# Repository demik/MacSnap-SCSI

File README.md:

# MacSnap SCSI

The MacSnap SCSI is an upgrade for the Macintosh 512K(e) It includes a SCSI controller and is designed to plug into the ROM slots
It was developed by Dove Computer Corporation. This is a REcreation with a few improvements.

<br />
<br />
<div align = center>
	
</div>

<br />
<br />
<br />
<br />

## [![Button Documentation]][Documentation]
- Kikad Files are located [here](EDA/REloaded), as well with building instructions for the REloaded board
- PLD files are located [here](PLD)
- Gerbers files are in the [release section](https://github.com/demik/MacSnap-SCSI/releases/download/v2.1/MacSnap_SCSI_Reloaded_2.1.zip)
- Schematic in PDF form is [here](https://github.com/demik/MacSnap-SCSI/blob/main/EDA/REloaded/MacSnap%20SCSI.pdf)

<!----------------------------------------------------------------------------->

[Documentation]: https://github.com/demik/MacSnap-SCSI/tree/main/EDA/REloaded/README.md

<!-------------------------------[ Buttons ]----------------------------------->

[Button Documentation]: https://img.shields.io/badge/Documentation-FFDD21?style=for-the-badge&logoColor=white&logo=opensourcehardware

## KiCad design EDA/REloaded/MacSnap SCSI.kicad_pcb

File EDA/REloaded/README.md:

# MacSnap SCSI Reloaded

This is a simple design clone to the original, using mostly all through hole components. It's designed this way to be period correct and easy to build for people who don't like soldering SMD components. The only SMD component is the 2.85V voltage regulator for SCSI termination.
Footprint is very similar. Like the original, the SCSI is provided through a LPT header.

The board has a few improvements:
- provides power to SCSI devices
- active SCSI termination
- voltage supervisor / reset ciruit

This folder contains the source KiKad files for this board.

## ![Button BOM]
### Mandatory

Here is the BOM for the board. Part number are what was tested on prototypes board but you may find alternatives easily, especially resistors and sockets

| Reference(s)          | Value      | Quantity | Notes                                  | Part number              |
|-----------------------|------------|----------|----------------------------------------|--------------------------|
| C1-2, C6, C7, C13-14  | 100nF      | 6        | Axial ceramic capacitor X7R            | Kemet C412C104K5R5TA7200 |
| C4                    | 1500pF     | 1        | Axial ceramic capacitor X7R 10%        | Kemet C410C152K1R5TA     |
| C8-11                 | 10uF       | 4        | Tantalum radial capacitor 2.5mm pitch  | Thomsen 481726           |
| D2                    | 1N5817     | 1        | Schottky Diode DO-15 20V               | Diotec 1N5817            |
| J1                    | 26 pins    | 1        | low profile shrouded IDC header        | TE Conn 5103309-6        |
| R1, R3                | 10kΩ       | 2        | standard 0.25W carbon film resistor    | TRU CFR0W4J0103          |
| R4                    | 470Ω       | 1        | standard 0.25W carbon film resistor    | TRU CFR0W4J0471          |
| R5, R6                | 47Ω        | 2        | standard 0.25W carbon film resistor    | TRU CFR0W4J0470          |
| RN1, RN2              | 110Ω       | 2        | 10 pins bussed resistor array          | Bourns 4610X-101-111LF   |
| U5, U6                | 16V8       | 2        | Programmable Logic Devices 15ns        | Microchip ATF16V8B-15PU  |
| U7                    | 53C80      | 1        | SCSI Interface IC 3MB/SEC CMOS SCSI I  | Zilog Z53C8003VSG        |
| U8                    | LDO        | 1        | 800mA SCSI-5 Active Terminator         | onsemi MC34268DR2G       |
| U10                   | RESET      | 1        | Supervisory Circuits 5V EconoReset     | DS1233D-15+              |
| -                     | LPT        | 1        | Parallel DB25 Female LPT to IDC 26-pin | ?? eBay / Amazon         |
| -                     | 14 pins    | 4        | Machine Pin break away header          | ?? eBay / Amazon         |
| Socket                | DIP-20     | 2        | THT DIP-20 socket                      | TRU TC-A 20-LC-TT-203    |
| Socket                | DIP-28     | 2        | THT DIP-28 socket                      | TRU TC-A 28-LC-TT-203    |
| Socket                | PLCC-44    | 1        | THT PLCC-44 socket                     | TRU TC-A-CCS 044-Z-T-203 |

Using sockets is recommended because it will allow you to reclaim both ROMs (to put back into factory) and PLDs

### Alternate

Both the 53C80 SCSI chip and MC34268 are obsolete components. NCR5380 in PLCC package is a working substitute. As for the active terminator LDO, there is an alternate build which consist of the following components:

| Reference(s)          | Value      | Quantity | Notes                                  | Part number              |
|-----------------------|------------|----------|----------------------------------------|--------------------------|
| U9                    | LDO        | 1        | LDO Voltage Regulators 800mA 2.85V     | A.D. LT1117CST-2.85      |
| C12                   | 10uF       | 1        | Tantalum radial capacitor 2.5mm pitch  | Thomsen 481726           |

When the LT1117CST build variant is used, do not populate U8

## ![Button Building]

PCB is 2 layers, the gerbers are avaible in the [release section](https://github.com/demik/MacSnap-SCSI/releases/download/v2.1/MacSnap_SCSI_Reloaded_2.1.zip)
You should be able to use any mainstream PCB manufacturer. Nothing special about this PCB, thickness should be 1.6mm

On JLCPCB, select _Create 2D barcode (Serial Number)_ to the option _Remove Order Number_. Others options to set:
- Printing: 2D barcode Only
- Code Type: QR Code
- Serial Number: MACSNAPSCSI
- QR Code Size: 10mm * 10mm
- QR Code Position: Specify Position

### Assembling

Building is straightworfard. You will need to start with the machine pin headers, then the following order is recommended:
- PDIP sockets
- axial resistors, axial capacitors
- resistors networks
- PLCC socket
- IDC header
- anything else left

### PLDs

You will need the following .jed files to program both ATF with this board:
- [DOV1b](../../PLD/DOV1B.jed) as DOV1b
- [DOV2_low](../../PLD/DOV2_low.jed) as DOV2

A TL866 II or T48 can program ATF16V8Bs just fine. Avoid ATF16V8BQL or ATF16V8C as this has not been tested and might lead into issues

### ROMs

Using real OEM ROMs is recommended. Replica ROMs do have different access timings, source and sink power capabilities, and thus may not work well with the MacSnap SCSI.
The following OEM sets have been tested without issues: 
- 342-0341-B & 342-0342-A
- 342-0341-C + 342-0342-B

<!-------------------------------[ Buttons ]----------------------------------->

[Button BOM]: https://img.shields.io/badge/BOM-FFDD21?style=for-the-badge&logoColor=white&logo=BookStack
[Button Building]: https://img.shields.io/badge/Building-FFDD21?style=for-the-badge&logoColor=white&logo=opensourcehardware

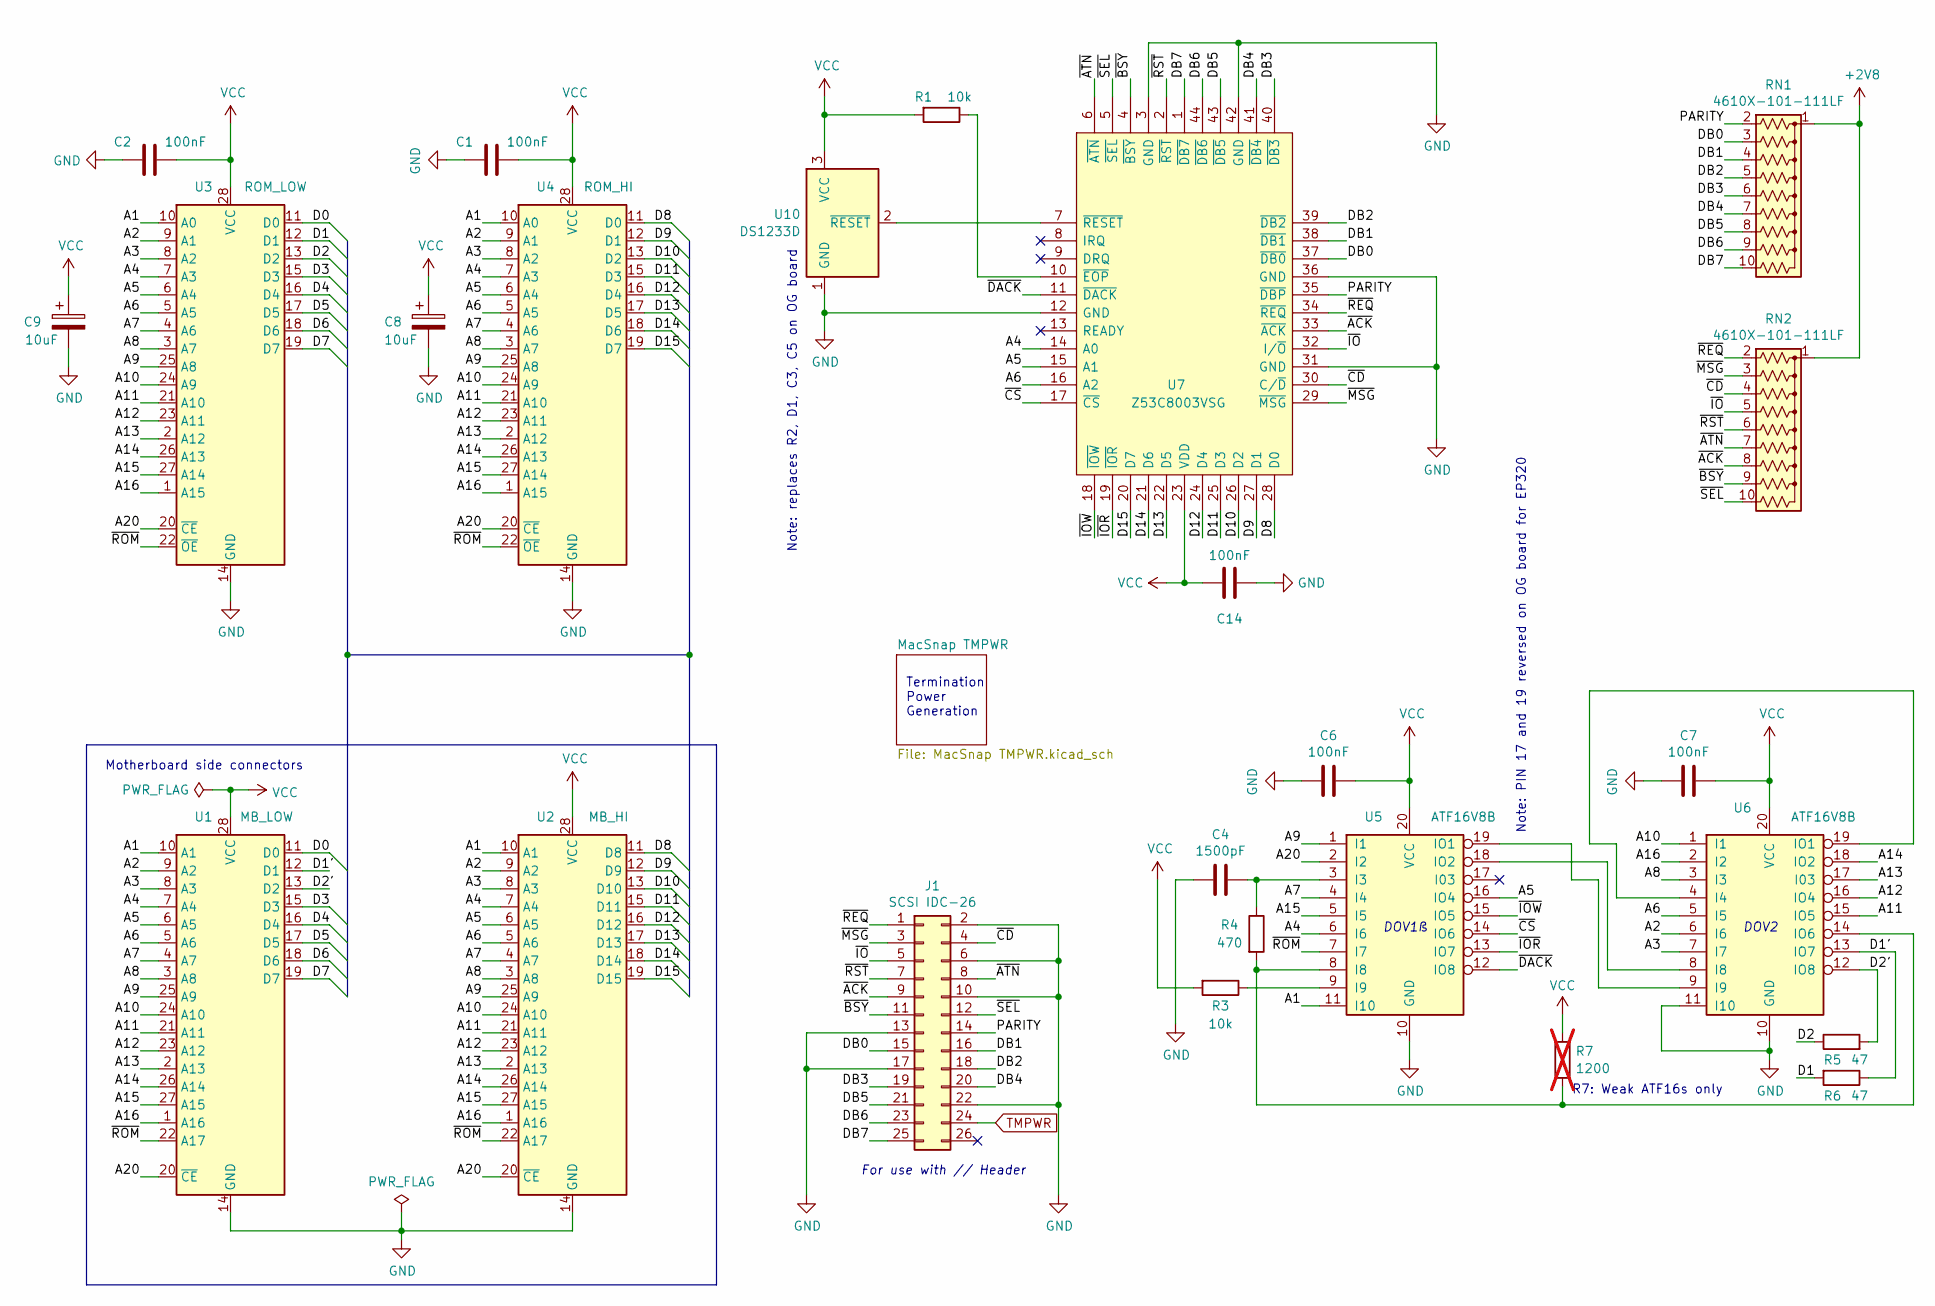
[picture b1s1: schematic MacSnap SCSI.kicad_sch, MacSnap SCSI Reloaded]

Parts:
C1, C2, C6, C7: 100nF; C_Axial_L3.8mm_D2.6mm_P7.50mm_Horizontal
C4: 1500pF; C_Axial_L3.8mm_D2.6mm_P7.50mm_Horizontal
C8, C9: 10uF; CP_Radial_Tantal_D4.5mm_P2.50mm
C14: 100nF; C_Axial_L3.8mm_D2.6mm_P10.00mm_Horizontal
J1: SCSI IDC-26; IDC-Header_2x13_P2.54mm_Vertical
R1, R3: 10k; R_Axial_DIN0207_L6.3mm_D2.5mm_P10.16mm_Horizontal
R4: 470; R_Axial_DIN0207_L6.3mm_D2.5mm_P10.16mm_Horizontal
R5, R6: 47; R_Axial_DIN0207_L6.3mm_D2.5mm_P10.16mm_Horizontal
R7: 1200; R_Axial_DIN0207_L6.3mm_D2.5mm_P10.16mm_Horizontal; not fitted
RN1, RN2: 4610X-101-111LF; R_Array_SIP10
U1: MB_LOW; DIP-28_W15.24mm_Piggy
U2: MB_HI; DIP-28_W15.24mm_Piggy
U3: ROM_LOW; DIP-28_W15.24mm_Socket
U4: ROM_HI; DIP-28_W15.24mm_Socket
U5, U6: ATF16V8B; DIP-20_W7.62mm
U7: Z53C8003VSG; PLCC-44_THT-Socket; Mouser Part Number 692-Z53C8003VSG
U10: DS1233D; TO-92_HandSolder

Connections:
+2V8: RN1.1 (common), RN2.1 (common); also elsewhere on the board
/A1: U1.10 (A1), U2.10 (A1), U3.10 (A0), U4.10 (A0), U5.11 (I10)
/A2: U1.9 (A2), U2.9 (A2), U3.9 (A1), U4.9 (A1), U6.6 (I6)
/A3: U1.8 (A3), U2.8 (A3), U3.8 (A2), U4.8 (A2), U6.7 (I7)
/A4: U1.7 (A4), U2.7 (A4), U3.7 (A3), U4.7 (A3), U5.6 (I6), U7.14 (A0)
/A5: U1.6 (A5), U2.6 (A5), U3.6 (A4), U4.6 (A4), U5.16 (IO4), U7.15 (A1)
/A6: U1.5 (A6), U2.5 (A6), U3.5 (A5), U4.5 (A5), U6.5 (I5), U7.16 (A2)
/A7: U1.4 (A7), U2.4 (A7), U3.4 (A6), U4.4 (A6), U5.4 (I4)
/A8: U1.3 (A8), U2.3 (A8), U3.3 (A7), U4.3 (A7), U6.3 (I3)
/A9: U1.25 (A9), U2.25 (A9), U3.25 (A8), U4.25 (A8), U5.1 (I1)
/A10: U1.24 (A10), U2.24 (A10), U3.24 (A9), U4.24 (A9), U6.1 (I1)
/A11: U1.21 (A11), U2.21 (A11), U3.21 (A10), U4.21 (A10), U6.15 (IO5)
/A12: U1.23 (A12), U2.23 (A12), U3.23 (A11), U4.23 (A11), U6.16 (IO4)
/A13: U1.2 (A13), U2.2 (A13), U3.2 (A12), U4.2 (A12), U6.17 (I03)
/A14: U1.26 (A14), U2.26 (A14), U3.26 (A13), U4.26 (A13), U6.18 (IO2)
/A15: U1.27 (A15), U2.27 (A15), U3.27 (A14), U4.27 (A14), U5.5 (I5)
/A16: U1.1 (A16), U2.1 (A16), U3.1 (A15), U4.1 (A15), U6.2 (I2)
/A20: U1.20 (~CE), U2.20 (~CE), U3.20 (~CE), U4.20 (~CE), U5.2 (I2)
/D0: U1.11 (D0), U3.11 (D0)
/D1: R6.2, U3.12 (D1)
/D1': R6.1, U1.12 (D1), U6.13 (IO7)
/D2: R5.1, U3.13 (D2)
/D2': R5.2, U1.13 (D2), U6.12 (IO8)
/D3: U1.15 (D3), U3.15 (D3)
/D4: U1.16 (D4), U3.16 (D4)
/D5: U1.17 (D5), U3.17 (D5)
/D6: U1.18 (D6), U3.18 (D6)
/D7: U1.19 (D7), U3.19 (D7)
/D8: U2.11 (D8), U4.11 (D0), U7.28 (D0)
/D9: U2.12 (D9), U4.12 (D1), U7.27 (D1)
/D10: U2.13 (D10), U4.13 (D2), U7.26 (D2)
/D11: U2.15 (D11), U4.15 (D3), U7.25 (D3)
/D12: U2.16 (D12), U4.16 (D4), U7.24 (D4)
/D13: U2.17 (D13), U4.17 (D5), U7.22 (D5)
/D14: U2.18 (D14), U4.18 (D6), U7.21 (D6)
/D15: U2.19 (D15), U4.19 (D7), U7.20 (D7)
/DB0: J1.15, RN1.3 (R2), U7.37 (~DB0)
/DB1: J1.16, RN1.4 (R3), U7.38 (~DB1)
/DB2: J1.18, RN1.5 (R4), U7.39 (~DB2)
/DB3: J1.19, RN1.6 (R5), U7.40 (~DB3)
/DB4: J1.20, RN1.7 (R6), U7.41 (~DB4)
/DB5: J1.21, RN1.8 (R7), U7.43 (~DB5)
/DB6: J1.23, RN1.9 (R8), U7.44 (~DB6)
/DB7: J1.25, RN1.10 (R9), U7.1 (~DB7)
/PARITY: J1.14, RN1.2 (R1), U7.35 (~DBP)
/~ACK: J1.9, RN2.8 (R7), U7.33 (~ACK)
/~ATN: J1.8, RN2.7 (R6), U7.6 (~ATN)
/~BSY: J1.11, RN2.9 (R8), U7.4 (~BSY)
/~CD: J1.4, RN2.4 (R3), U7.30 (C/~D)
/~CS: U5.14 (IO6), U7.17 (~CS)
/~DACK: U5.12 (IO8), U7.11 (~DACK)
/~IOR: U5.13 (IO7), U7.19 (~IOR)
/~IOW: U5.15 (IO5), U7.18 (~IOW)
/~IO: J1.5, RN2.5 (R4), U7.32 (I/~O)
/~MSG: J1.3, RN2.3 (R2), U7.29 (~MSG)
/~REQ: J1.1, RN2.2 (R1), U7.34 (~REQ)
/~ROM: U1.22 (A17), U2.22 (A17), U3.22 (~OE), U4.22 (~OE), U5.7 (I7)
/~RST: J1.7, RN2.6 (R5), U7.2 (~RST)
/~SEL: J1.12, RN2.10 (R9), U7.5 (~SEL)
GND: C1.2, C2.2, C4.2, C6.2, C7.2, C8.2, C9.2, C14.2, J1.2, J1.6, J1.10, J1.13, J1.17, J1.22, U1.14 (GND), U2.14 (GND), U3.14 (GND), U4.14 (GND), U5.10 (GND), U6.10 (GND), U6.11 (I10), U7.3 (GND), U7.12 (GND), U7.31 (GND), U7.36 (GND), U7.42 (GND), U10.1 (GND); also elsewhere on the board
unnamed: C4.1, R4.1, U5.3 (I3)
unnamed: R4.2, R7.2, U5.8 (I8), U6.14 (IO6)
unnamed: R3.1, U5.9 (I9)
unnamed: U5.19 (IO1), U6.9 (I9)
unnamed: U5.18 (IO2), U6.8 (I8)
unnamed: U6.4 (I4), U6.19 (IO1)
unnamed: R1.1, U7.10 (~EOP)
unnamed: U7.7 (~RESET), U10.2 (~RESET)
TMPWR: J1.24; also elsewhere on the board
VCC: C1.1, C2.1, C6.1, C7.1, C8.1, C9.1, C14.1, R1.2, R3.2, R7.1, U1.28 (VCC), U2.28 (VCC), U3.28 (VCC), U4.28 (VCC), U5.20 (VCC), U6.20 (VCC), U7.23 (VDD), U10.3 (VCC); also elsewhere on the board

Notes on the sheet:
R7: Weak ATF16s only
Termination Power Generation
DOV1ß
Note: replaces R2, D1, C3, C5 on OG board
Motherboard side connectors
For use with // Header
Note: PIN 17 and 19 reversed on OG board for EP320
DOV2

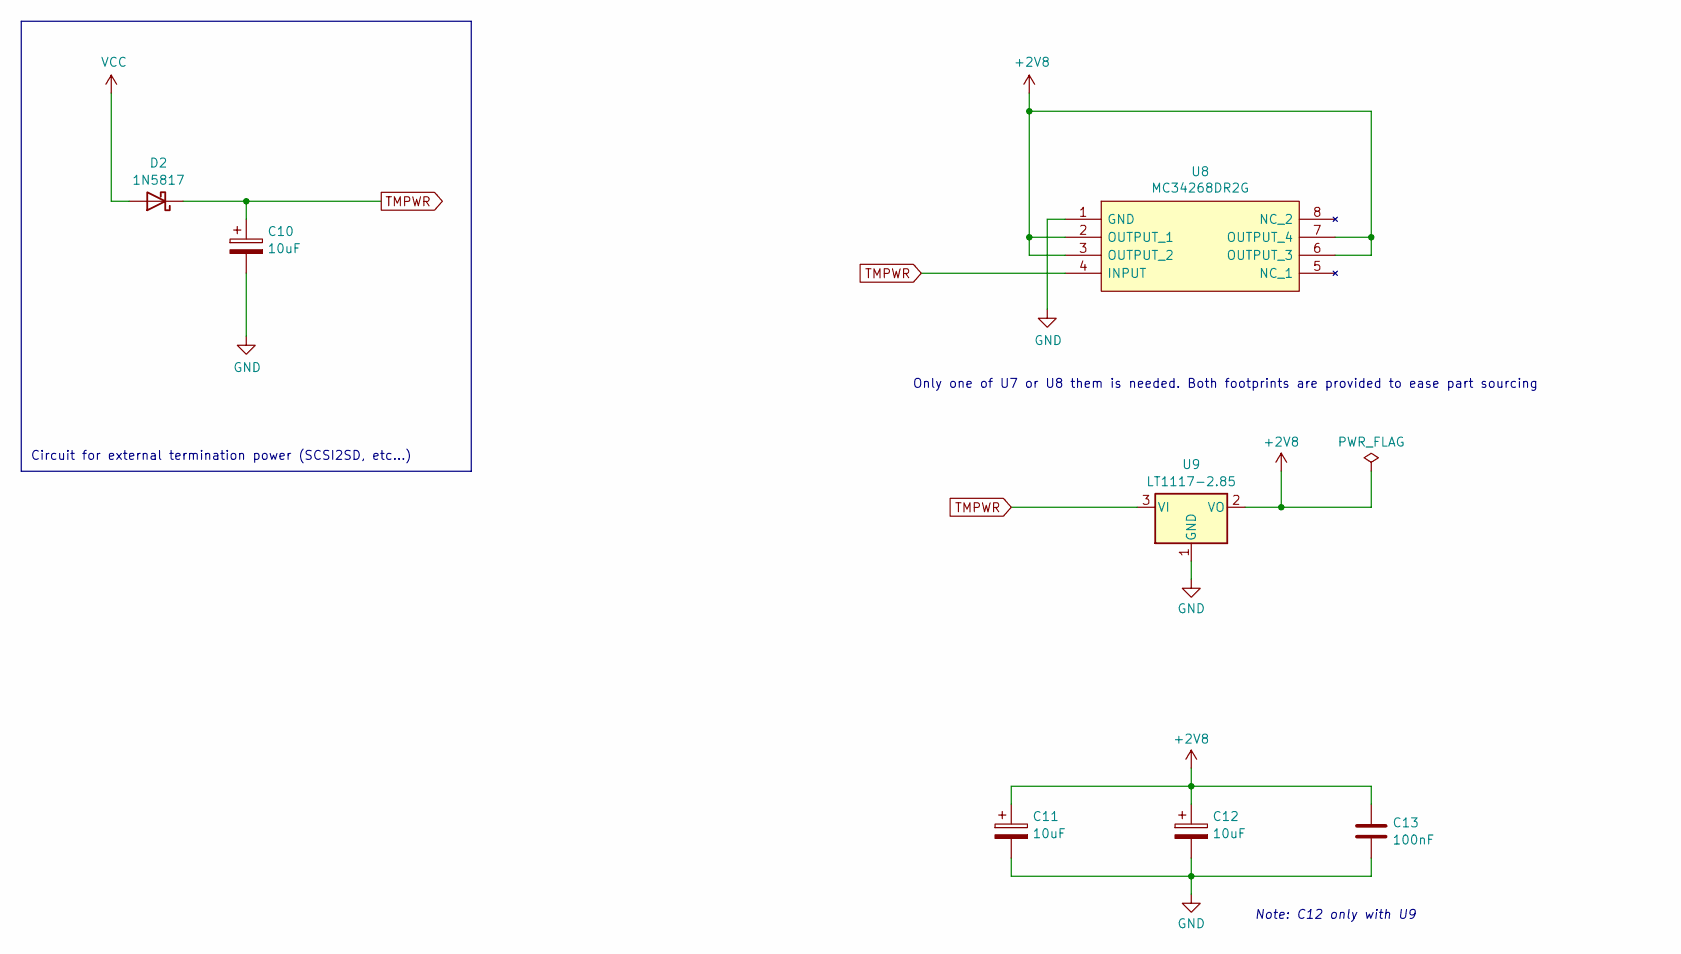
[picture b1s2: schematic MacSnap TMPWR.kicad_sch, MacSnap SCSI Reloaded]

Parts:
C10, C11, C12: 10uF; CP_Radial_Tantal_D4.5mm_P2.50mm
C13: 100nF; C_Axial_L3.8mm_D2.6mm_P10.00mm_Horizontal
D2: 1N5817; D_DO-41_SOD81_P10.16mm_Horizontal
U8: MC34268DR2G; SOIC-8_3.9x4.9mm_P1.27mm; Mouser Part Number 863-MC34268DR2G
U9: LT1117-2.85; SOT-223-3_TabPin2

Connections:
+2V8: C11.1, C12.1, C13.1, U8.2 (OUTPUT_1), U8.3 (OUTPUT_2), U8.6 (OUTPUT_3), U8.7 (OUTPUT_4), U9.2 (VO); also elsewhere on the board
GND: C10.2, C11.2, C12.2, C13.2, U8.1 (GND), U9.1 (GND); also elsewhere on the board
TMPWR: C10.1, D2.1 (K), U8.4 (INPUT), U9.3 (VI); also elsewhere on the board
VCC: D2.2 (A); also elsewhere on the board

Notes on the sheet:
Circuit for external termination power (SCSI2SD, etc…)
Only one of U7 or U8 them is needed. Both footprints are provided to ease part sourcing
Note: C12 only with U9

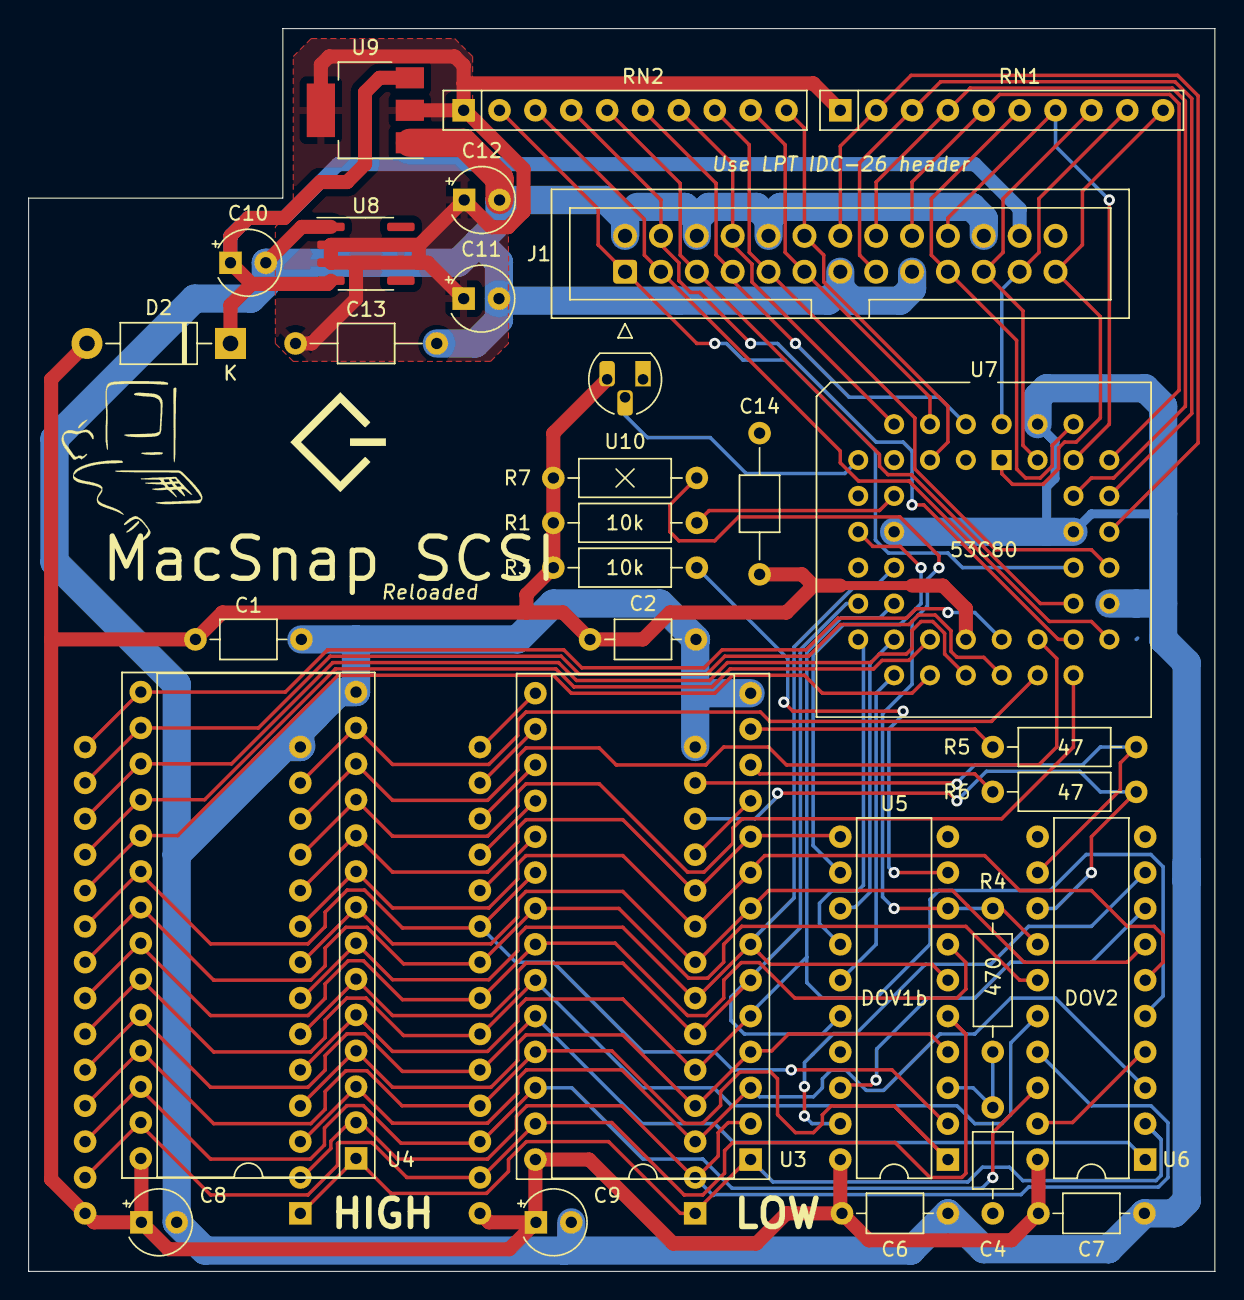
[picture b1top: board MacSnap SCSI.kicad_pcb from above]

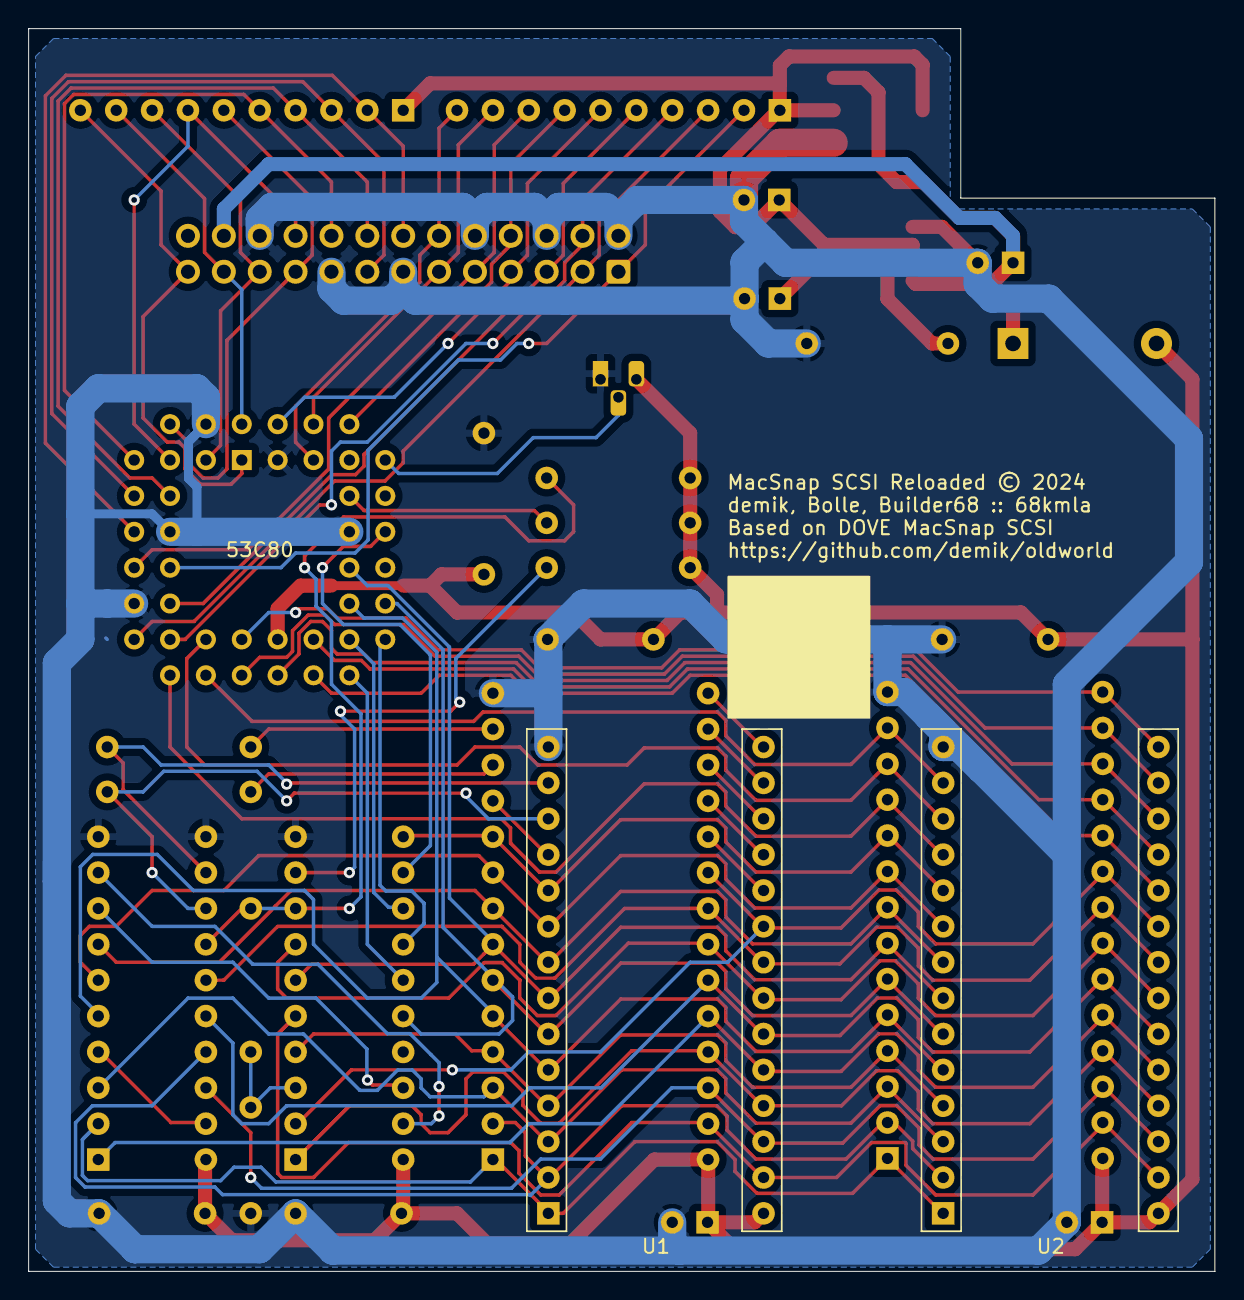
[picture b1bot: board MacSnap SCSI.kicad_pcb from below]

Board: 2 copper layers, 84.0 x 88.0 mm, 32 parts (2 on the bottom side), 70 nets.

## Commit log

2025-03-13 Update LICENSE
2025-03-13 added original schematics by Builder68
2025-03-14 added PLD stuff
2025-03-14 Initial REloaded public release
2025-03-15 removed backups files
2025-03-15 added main README.md
2025-03-15 formating
2025-03-16 added building instructions
2025-03-16 fixed image link
2025-03-16 fixed building button
2025-03-17 fixed typo
2025-03-17 added LPT header photo
2025-03-17 added machine pin headers picture
2025-04-08 added PLD dump picture
2025-05-17 Update README.md
    added note about the improvements
2025-07-22 added note about ROMs
2025-07-22 Update README.md
    Formating ROMs

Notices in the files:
EDA/REloaded/MacSnap SCSI.kicad_pcb:
MacSnap SCSI Reloaded © 2024
